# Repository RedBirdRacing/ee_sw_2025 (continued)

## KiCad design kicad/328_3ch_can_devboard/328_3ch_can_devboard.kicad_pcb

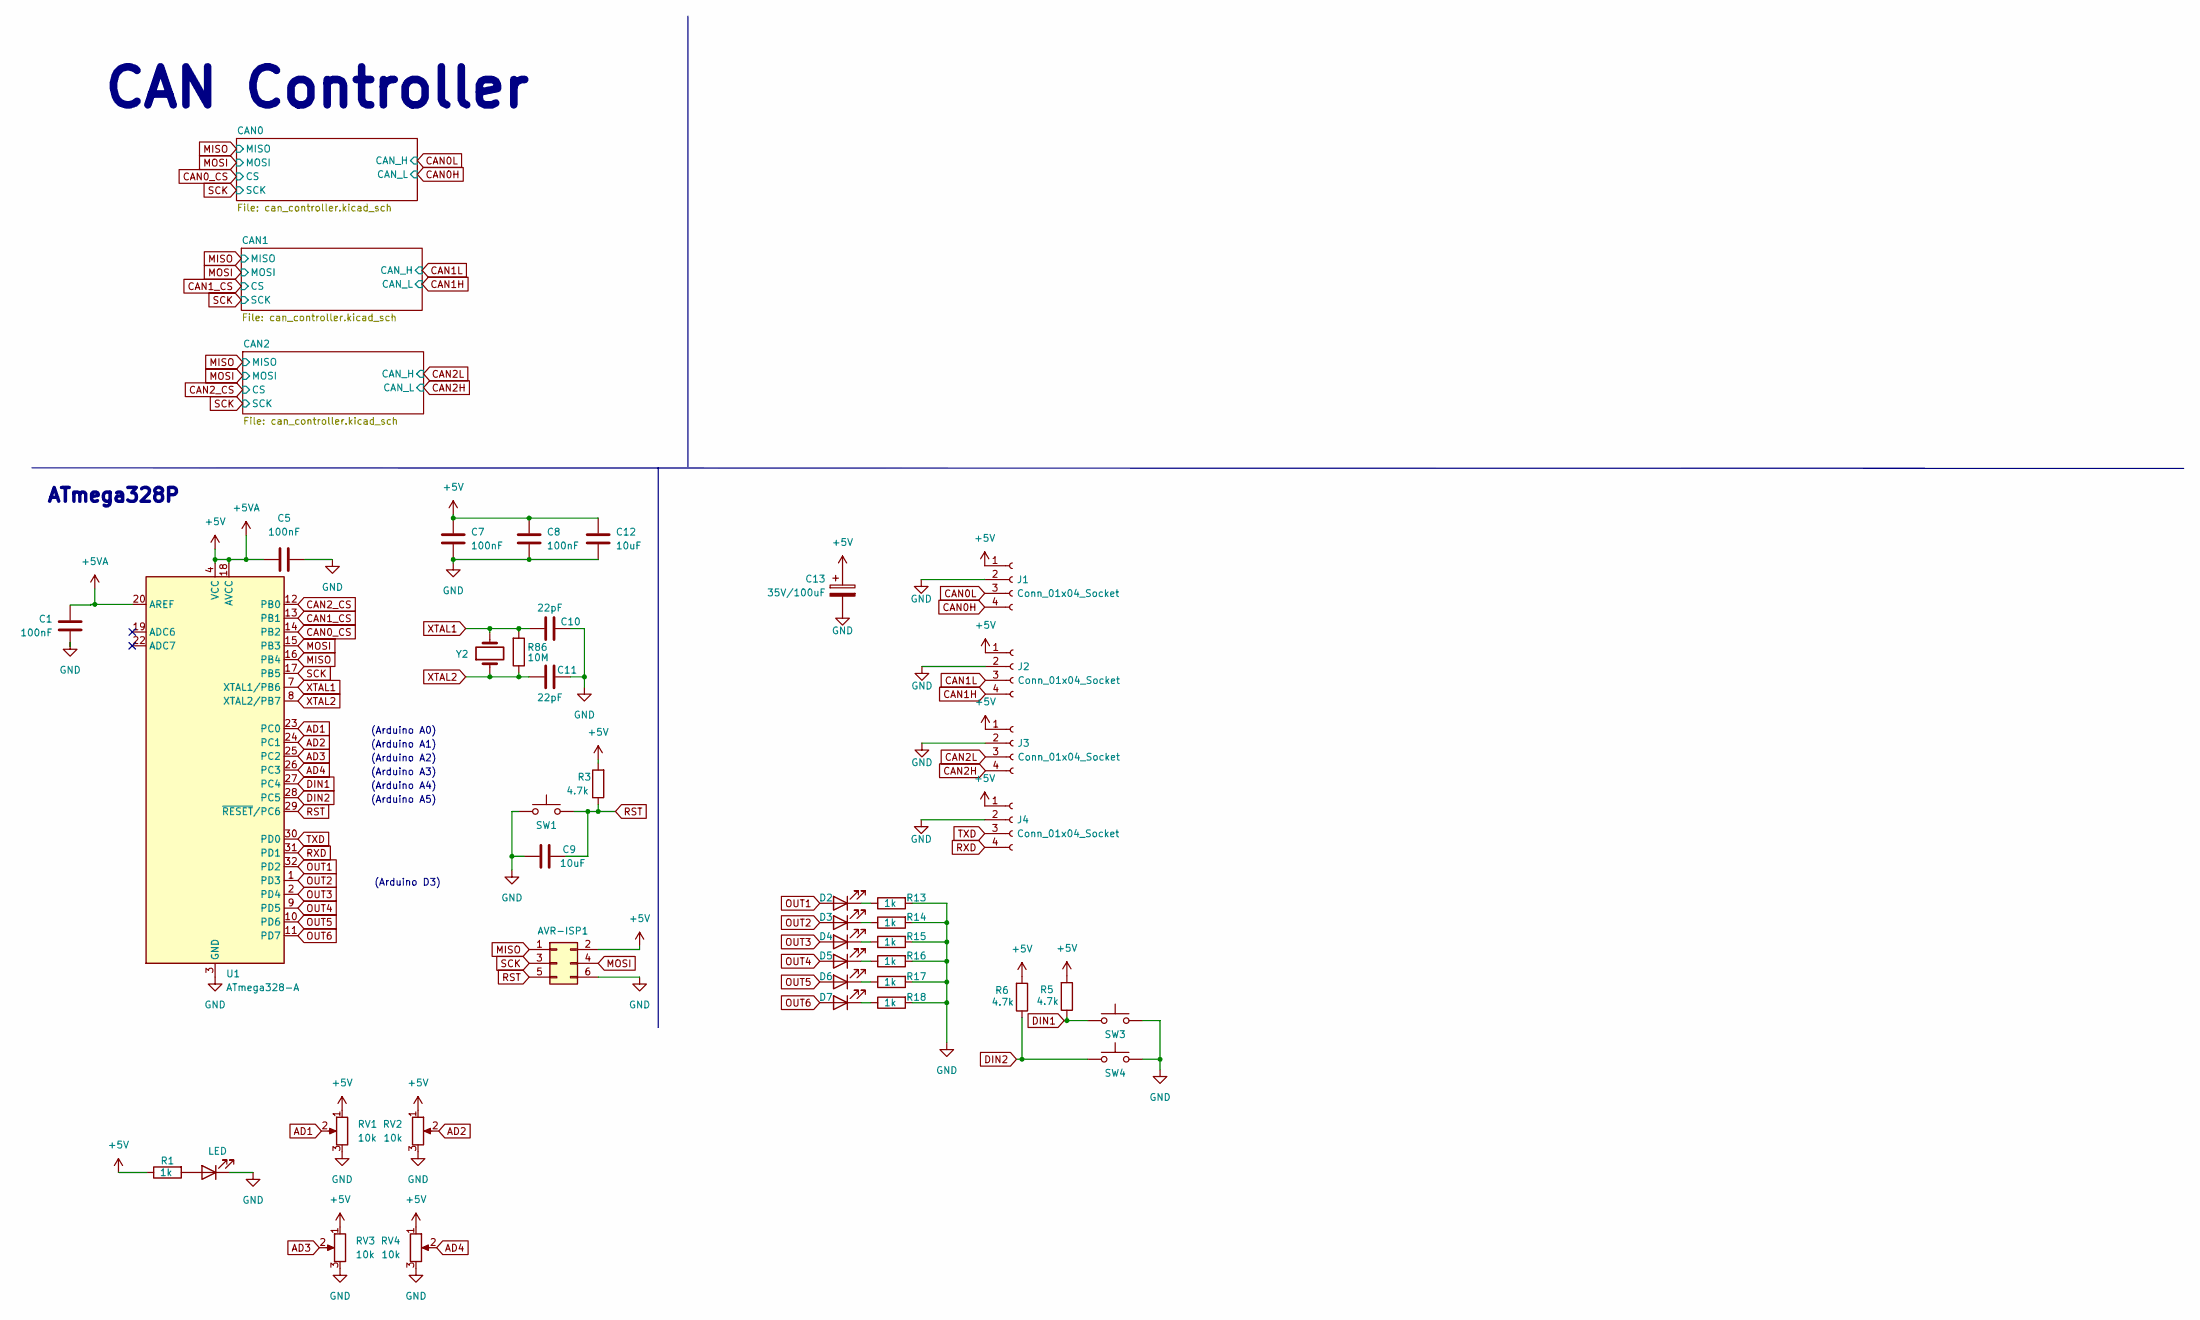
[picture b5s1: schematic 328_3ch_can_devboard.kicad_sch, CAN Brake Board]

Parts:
AVR-ISP1: Conn_02x03_Odd_Even; PinHeader_2x03_P2.54mm_Vertical
C1, C5, C7, C8: 100nF; C_0805_2012Metric_Pad1.18x1.45mm_HandSolder_L
C9, C12: 10uF; C_0805_2012Metric_Pad1.18x1.45mm_HandSolder_L
C10, C11: 22pF; C_0805_2012Metric_Pad1.18x1.45mm_HandSolder_L
C13: 35V/100uF; CP_Radial_D6.3mm_P2.50mm
D1, D2, D3, D4, D5, D6, D7: LED; LED_0805_2012Metric_Pad1.15x1.40mm_HandSolder
J1, J2, J3, J4: Conn_01x04_Socket; JST_XH_B4B-XH-A_1x04_P2.50mm_Vertical
R1, R13, R14, R15, R16, R17, R18: 1k; R_0805_2012Metric_Pad1.20x1.40mm_HandSolder_L
R3, R5, R6: 4.7k; R_0805_2012Metric_Pad1.20x1.40mm_HandSolder_L
R86: 10M; R_0805_2012Metric_Pad1.20x1.40mm_HandSolder_L
RV1, RV2, RV3, RV4: 10k; TRIM_3362P-1-103
SW1: SW_Push; SW_SPST_CK_RS282G05A3
SW3, SW4: SW_Push; SW_PUSH_6mm_H5mm
U1: ATmega328-A; TQFP-32_7x7mm_P0.8mm_L
Y2: 20MHz; Crystal_HC49-U_Vertical_W_SMD

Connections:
+5V: AVR-ISP1.2, C1.2, C5.2, C7.2, C8.2, C12.2, C13.1, J1.1, J2.1, J3.1, J4.1, R1.1, R3.2, R5.2, R6.2, RV1.1, RV2.1, RV3.1, RV4.1, U1.4 (VCC), U1.6 (VCC), U1.18 (AVCC), U1.20 (AREF); also elsewhere on the board
AD1: RV1.2, U1.23 (PC0)
AD2: RV2.2, U1.24 (PC1)
AD3: RV3.2, U1.25 (PC2)
AD4: RV4.2, U1.26 (PC3)
CAN0H: J1.4; also elsewhere on the board
CAN0L: J1.3; also elsewhere on the board
CAN0_CS: U1.14 (PB2); also elsewhere on the board
CAN1H: J2.4; also elsewhere on the board
CAN1L: J2.3; also elsewhere on the board
CAN1_CS: U1.13 (PB1); also elsewhere on the board
CAN2H: J3.4; also elsewhere on the board
CAN2L: J3.3; also elsewhere on the board
CAN2_CS: U1.12 (PB0); also elsewhere on the board
DIN1: R5.1, SW3.1, U1.27 (PC4)
DIN2: R6.1, SW4.1, U1.28 (PC5)
GND: AVR-ISP1.6, C1.1, C5.1, C7.1, C8.1, C9.1, C10.1, C11.1, C12.1, C13.2, D1.1 (K), J1.2, J2.2, J3.2, J4.2, R13.2, R14.2, R15.2, R16.2, R17.2, R18.2, RV1.3, RV2.3, RV3.3, RV4.3, SW1.1, SW3.2, SW4.2, U1.3 (GND), U1.5 (GND), U1.21 (GND); also elsewhere on the board
MISO: AVR-ISP1.1, U1.16 (PB4); also elsewhere on the board
MOSI: AVR-ISP1.4, U1.15 (PB3); also elsewhere on the board
unnamed: D1.2 (A), R1.2
unnamed: D2.1 (K), R13.1
unnamed: D3.1 (K), R14.1
unnamed: D4.1 (K), R15.1
unnamed: D5.1 (K), R16.1
unnamed: D6.1 (K), R17.1
unnamed: D7.1 (K), R18.1
OUT1: D2.2 (A), U1.32 (PD2)
OUT2: D3.2 (A), U1.1 (PD3)
OUT3: D4.2 (A), U1.2 (PD4)
OUT4: D5.2 (A), U1.9 (PD5)
OUT5: D6.2 (A), U1.10 (PD6)
OUT6: D7.2 (A), U1.11 (PD7)
RST: AVR-ISP1.5, C9.2, R3.1, SW1.2, U1.29 (~RESET/PC6)
RXD: J4.4, U1.31 (PD1)
SCK: AVR-ISP1.3, U1.17 (PB5); also elsewhere on the board
TXD: J4.3, U1.30 (PD0)
XTAL1: C10.2, R86.2, U1.7 (XTAL1/PB6), Y2.2
XTAL2: C11.2, R86.1, U1.8 (XTAL2/PB7), Y2.1

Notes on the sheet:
(Arduino A4)
(Arduino A2)
ATmega328P
(Arduino A0)
(Arduino D3)
(Arduino A5)
CAN Controller
(Arduino A1)
(Arduino A3)

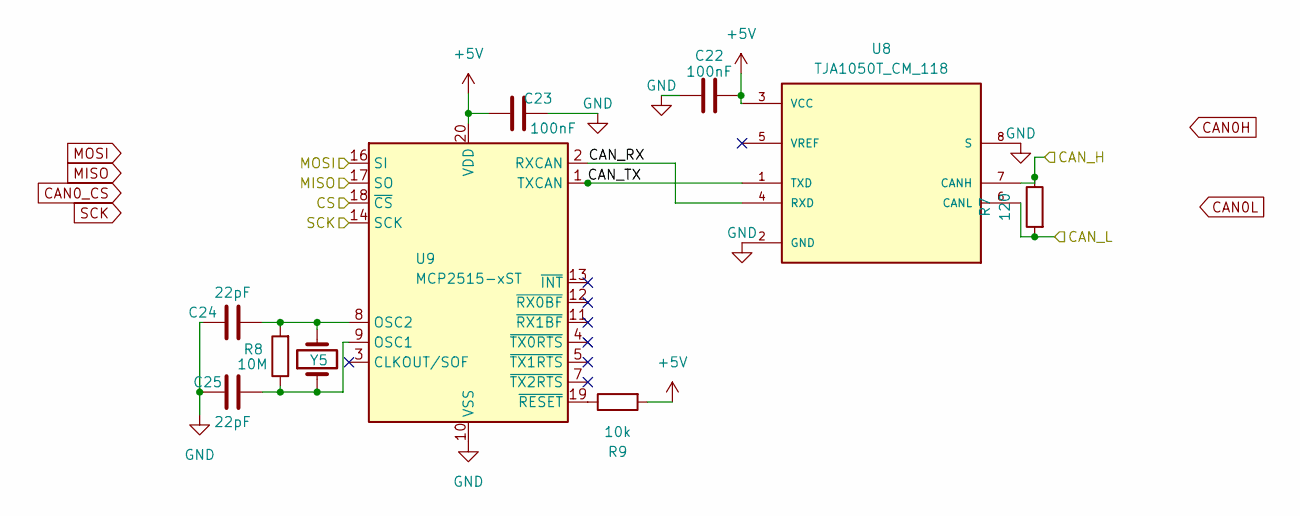
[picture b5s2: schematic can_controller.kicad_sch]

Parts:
C22, C23: 100nF; C_0805_2012Metric_Pad1.18x1.45mm_HandSolder_L
C24, C25: 22pF; C_0805_2012Metric_Pad1.18x1.45mm_HandSolder_L
R7: 120; R_0805_2012Metric_Pad1.20x1.40mm_HandSolder_L
R8: 10M; R_0805_2012Metric_Pad1.20x1.40mm_HandSolder_L
R9: 10k; R_0805_2012Metric_Pad1.20x1.40mm_HandSolder_L
U8: TJA1050T_CM_118; SOIC127P600X175-8N; PARTREV 4
U9: MCP2515-xST; TSSOP-20_4.4x6.5mm_P0.65mm
Y5: 20MHz; Crystal_HC49-U_Vertical_W_SMD

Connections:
+5V: C22.2, C23.2, R9.2, U8.3 (VCC), U9.20 (VDD); also elsewhere on the board
/CAN0/CAN_RX: U8.4 (RXD), U9.2 (RXCAN)
/CAN0/CAN_TX: U8.1 (TXD), U9.1 (TXCAN)
CAN0H: R7.2, U8.6 (CANL); also elsewhere on the board
CAN0L: R7.1, U8.7 (CANH); also elsewhere on the board
CAN0_CS: U9.18 (~CS); also elsewhere on the board
GND: C22.1, C23.1, C24.1, C25.1, U8.2 (GND), U8.8 (S), U9.10 (VSS); also elsewhere on the board
MISO: U9.17 (SO); also elsewhere on the board
MOSI: U9.16 (SI); also elsewhere on the board
unnamed: C25.2, R8.1, U9.9 (OSC1), Y5.1
unnamed: C24.2, R8.2, U9.8 (OSC2), Y5.2
unnamed: R9.1, U9.19 (~RESET)
SCK: U9.14 (SCK); also elsewhere on the board

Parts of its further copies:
C2, C3, C14, C15: 100nF; C_0805_2012Metric_Pad1.18x1.45mm_HandSolder_L
C4, C6, C16, C17: 22pF; C_0805_2012Metric_Pad1.18x1.45mm_HandSolder_L
R2, R11: 120; R_0805_2012Metric_Pad1.20x1.40mm_HandSolder_L
R4, R12: 10M; R_0805_2012Metric_Pad1.20x1.40mm_HandSolder_L
R10, R19: 10k; R_0805_2012Metric_Pad1.20x1.40mm_HandSolder_L
U2, U4: TJA1050T_CM_118; SOIC127P600X175-8N; PARTREV 4
U3, U5: MCP2515-xST; TSSOP-20_4.4x6.5mm_P0.65mm
Y1, Y3: 20MHz; Crystal_HC49-U_Vertical_W_SMD

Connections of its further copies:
+5V: C2.2, C3.2, C14.2, C15.2, R10.2, R19.2, U2.3 (VCC), U3.20 (VDD), U4.3 (VCC), U5.20 (VDD); also elsewhere on the board
/CAN1/CAN_RX: U2.4 (RXD), U3.2 (RXCAN)
/CAN1/CAN_TX: U2.1 (TXD), U3.1 (TXCAN)
/CAN2/CAN_RX: U4.4 (RXD), U5.2 (RXCAN)
/CAN2/CAN_TX: U4.1 (TXD), U5.1 (TXCAN)
CAN1H: R2.2, U2.6 (CANL); also elsewhere on the board
CAN1L: R2.1, U2.7 (CANH); also elsewhere on the board
CAN1_CS: U3.18 (~CS); also elsewhere on the board
CAN2H: R11.2, U4.6 (CANL); also elsewhere on the board
CAN2L: R11.1, U4.7 (CANH); also elsewhere on the board
CAN2_CS: U5.18 (~CS); also elsewhere on the board
GND: C2.1, C3.1, C4.1, C6.1, C14.1, C15.1, C16.1, C17.1, U2.2 (GND), U2.8 (S), U3.10 (VSS), U4.2 (GND), U4.8 (S), U5.10 (VSS); also elsewhere on the board
MISO: U3.17 (SO), U5.17 (SO); also elsewhere on the board
MOSI: U3.16 (SI), U5.16 (SI); also elsewhere on the board
unnamed: C6.2, R4.1, U3.9 (OSC1), Y1.1
unnamed: C4.2, R4.2, U3.8 (OSC2), Y1.2
unnamed: R10.1, U3.19 (~RESET)
unnamed: C17.2, R12.1, U5.9 (OSC1), Y3.1
unnamed: C16.2, R12.2, U5.8 (OSC2), Y3.2
unnamed: R19.1, U5.19 (~RESET)
SCK: U3.14 (SCK), U5.14 (SCK); also elsewhere on the board

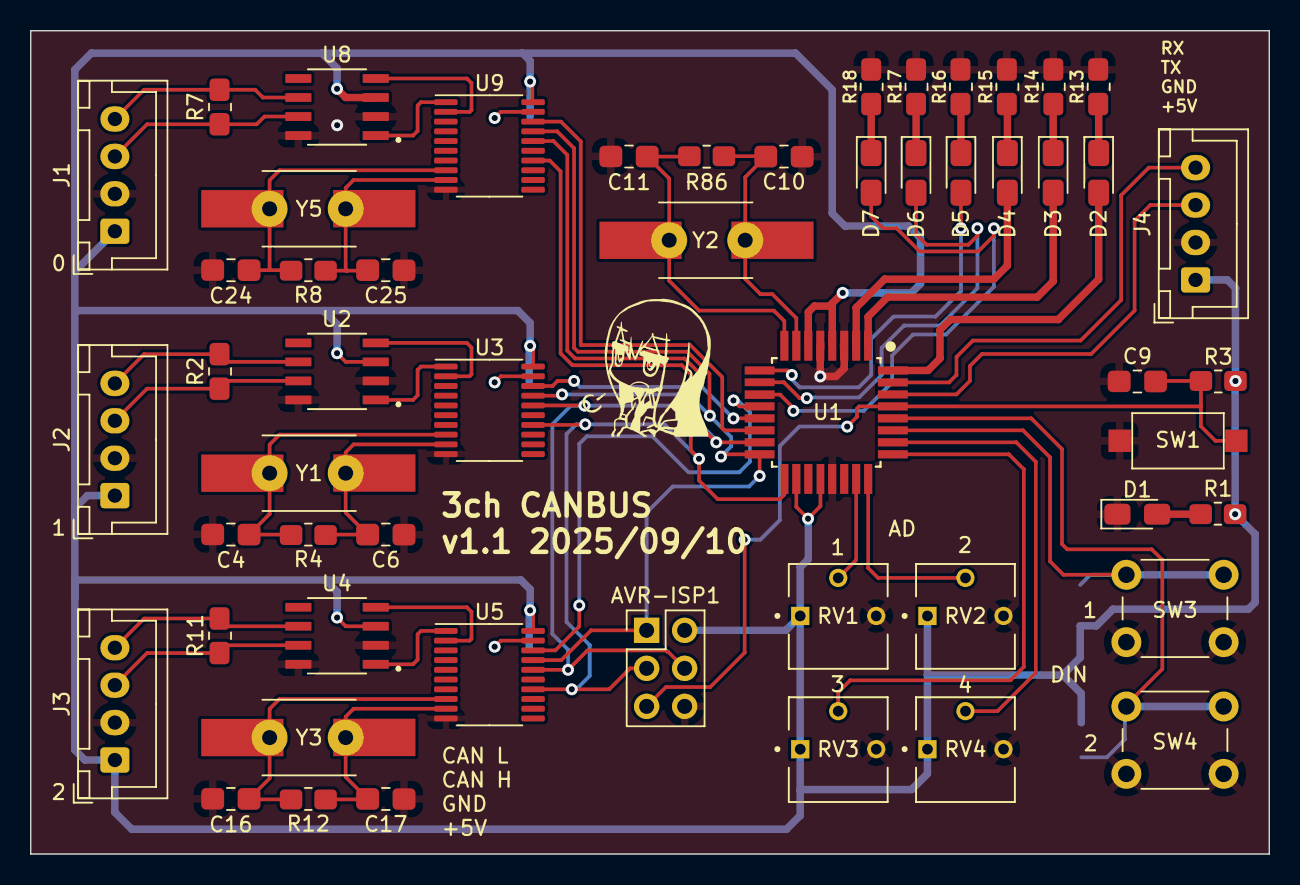
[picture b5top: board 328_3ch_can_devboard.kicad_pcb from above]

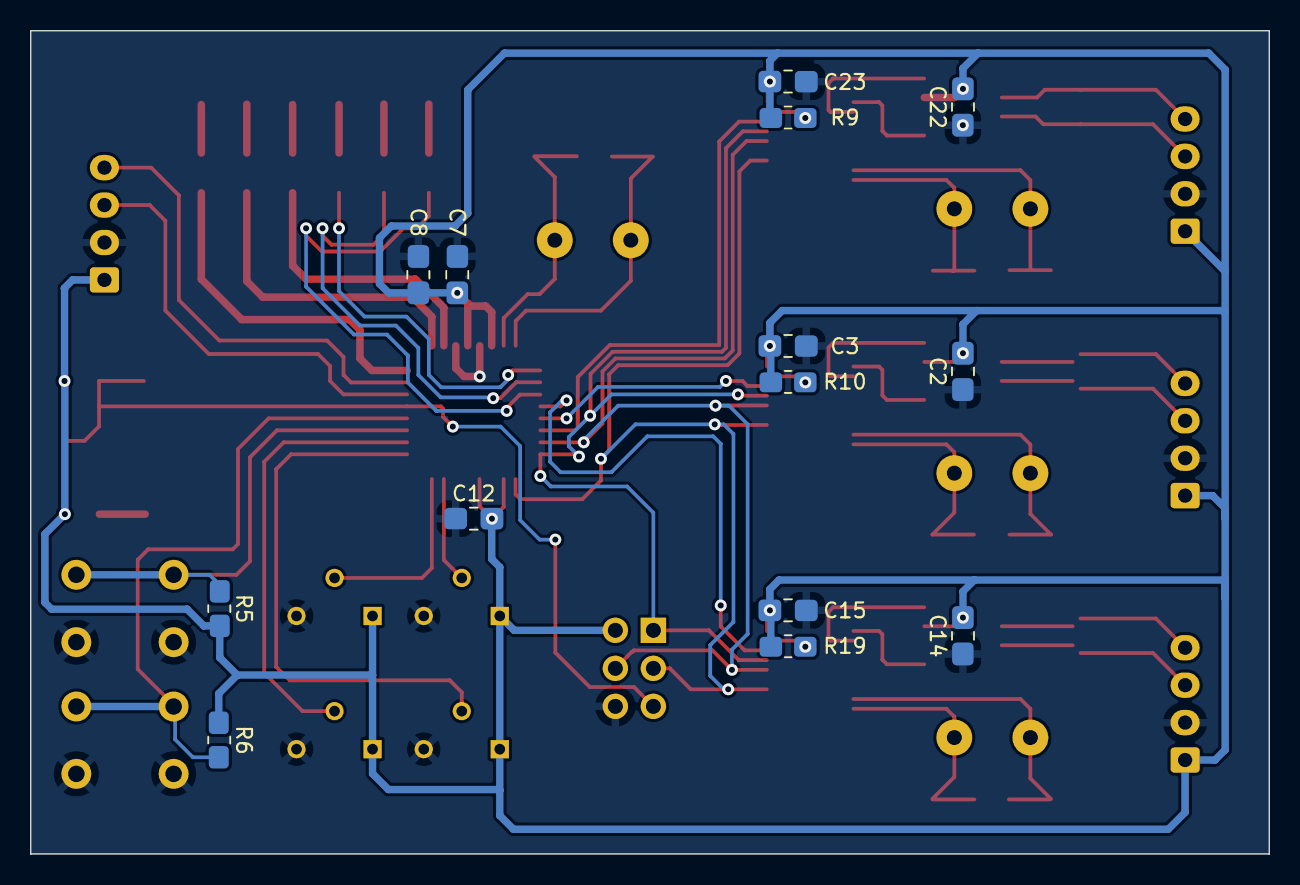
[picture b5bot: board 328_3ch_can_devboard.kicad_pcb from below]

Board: 2 copper layers, 82.8 x 55.0 mm, 69 parts (14 on the bottom side), 53 nets.

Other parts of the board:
G0: LOGO

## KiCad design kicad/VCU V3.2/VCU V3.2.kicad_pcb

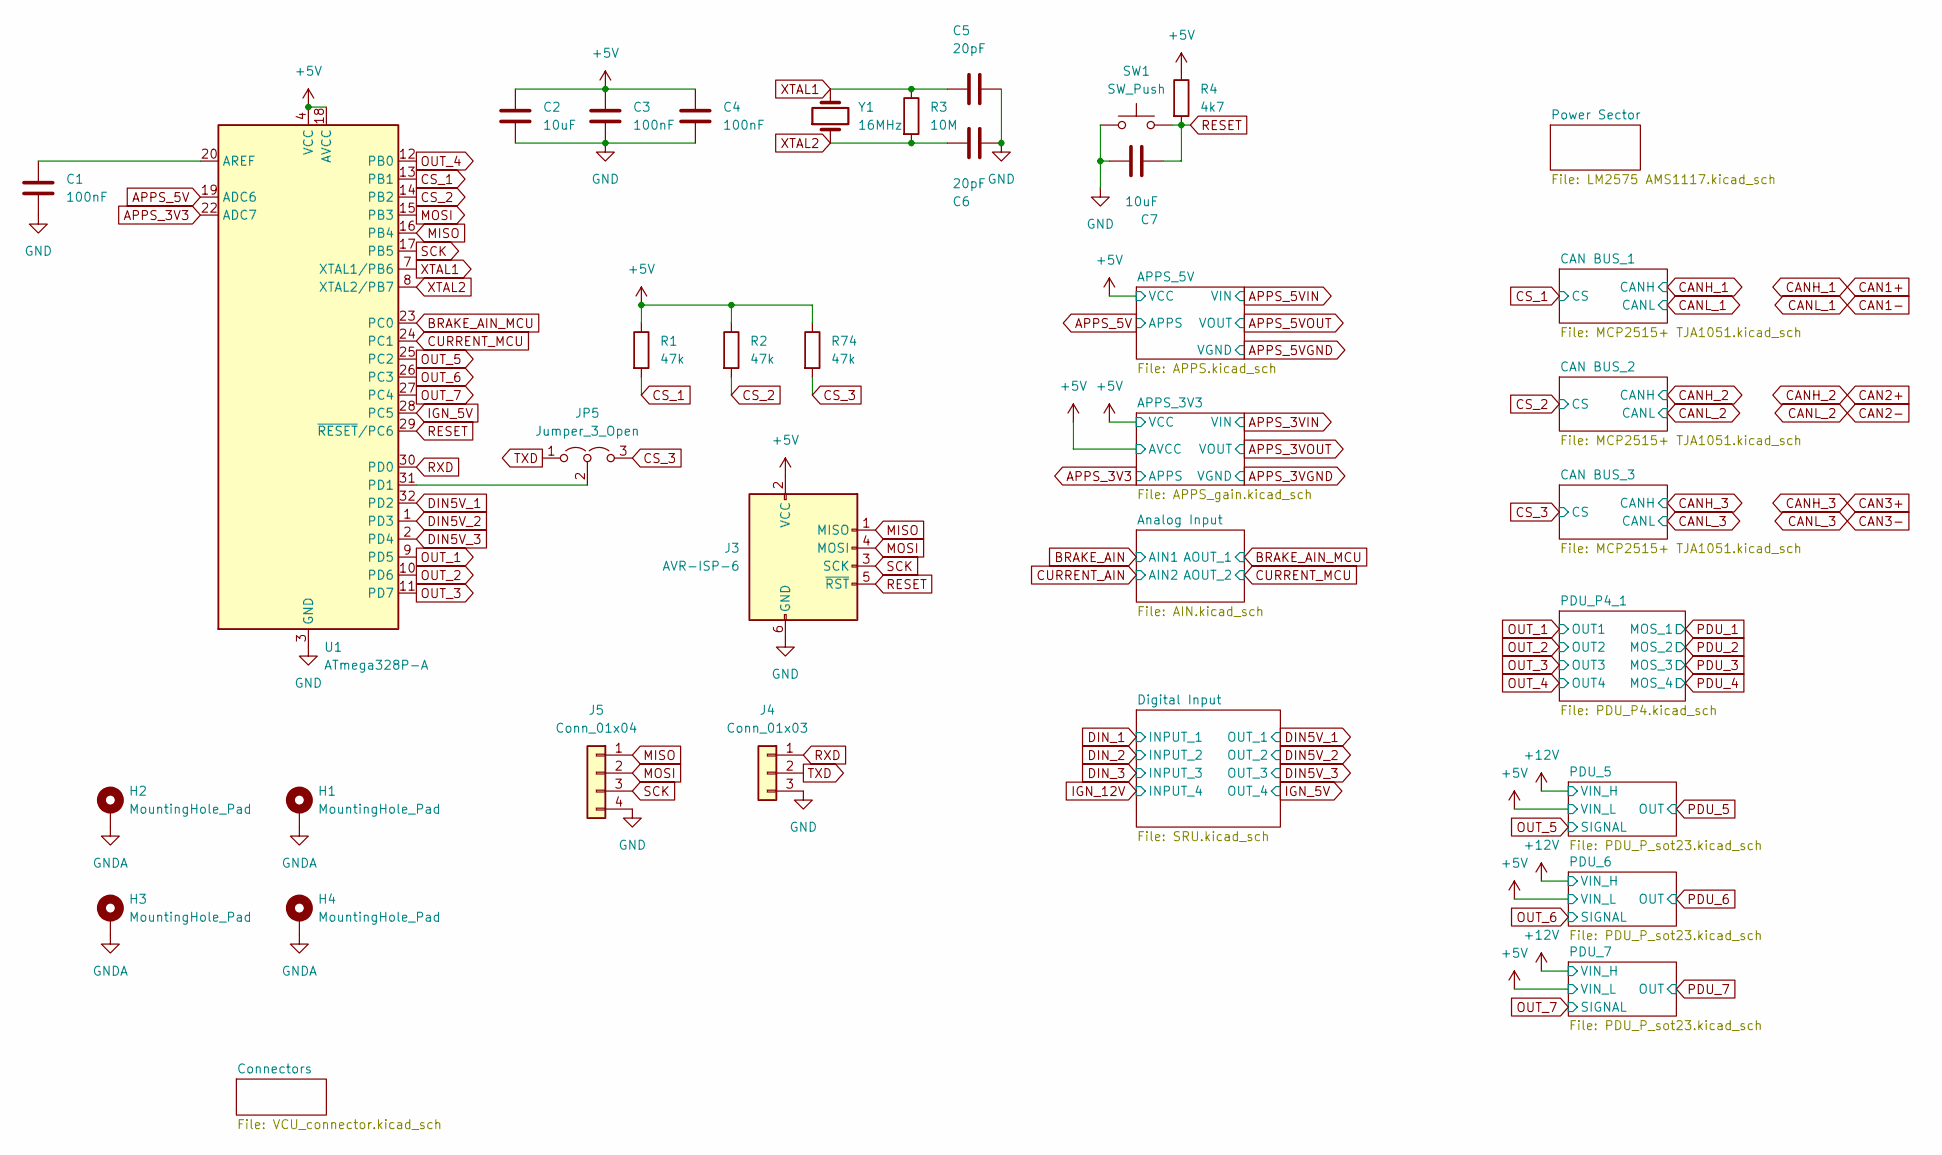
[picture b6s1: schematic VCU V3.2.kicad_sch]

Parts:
C1, C3, C4: 100nF; C_0805_2012Metric_Pad1.18x1.45mm_HandSolder_L
C2, C7: 10uF; C_0805_2012Metric_Pad1.18x1.45mm_HandSolder_L
C5, C6: 20pF; C_0805_2012Metric_Pad1.18x1.45mm_HandSolder_L
H1, H2, H3, H4: MountingHole_Pad; MountingHole_3.2mmx5mm_M3_ISO7380
J3: AVR-ISP-6; PinHeader_2x03_P2.54mm_Vertical_handsolder
J4: Conn_01x03; JST_XH_B3B-XH-A_1x03_P2.50mm_Vertical
J5: Conn_01x04; JST_XH_B4B-XH-A_1x04_P2.50mm_Vertical
JP5: Jumper_3_Open; SolderJumper-3_P1.3mm_Open_Pad1.0x1.5mm
R1, R2, R74: 47k; R_0805_2012Metric_Pad1.20x1.40mm_HandSolder_L
R3: 10M; R_0805_2012Metric_Pad1.20x1.40mm_HandSolder_L
R4: 4k7; R_0805_2012Metric_Pad1.20x1.40mm_HandSolder_L
SW1: SW_Push; SW_PUSH_6mm
U1: ATmega328P-A; TQFP-32_7x7mm_P0.8mm_L
Y1: 16MHz; Crystal_HC49-U_Vertical_W_SMD_Handolder

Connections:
+5V: C2.1, C3.1, C4.1, J3.2 (VCC), R1.1, R2.1, R4.1, R74.1, U1.4 (VCC), U1.6 (VCC), U1.18 (AVCC); also elsewhere on the board
APPS_3V3: U1.22 (ADC7); also elsewhere on the board
APPS_5V: U1.19 (ADC6); also elsewhere on the board
BRAKE_AIN_MCU: U1.23 (PC0); also elsewhere on the board
CS_1: R1.2, U1.13 (PB1); also elsewhere on the board
CS_2: R2.2, U1.14 (PB2); also elsewhere on the board
CS_3: JP5.3 (B), R74.2; also elsewhere on the board
CURRENT_MCU: U1.24 (PC1); also elsewhere on the board
DIN5V_1: U1.32 (PD2); also elsewhere on the board
DIN5V_2: U1.1 (PD3); also elsewhere on the board
DIN5V_3: U1.2 (PD4); also elsewhere on the board
GND: C1.2, C2.2, C3.2, C4.2, C5.2, C6.2, C7.2, J3.6 (GND), J4.3, J5.4, SW1.1, U1.3 (GND), U1.5 (GND), U1.21 (GND); also elsewhere on the board
IGN_5V: U1.28 (PC5); also elsewhere on the board
MISO: J3.1 (MISO), J5.1, U1.16 (PB4); also elsewhere on the board
MOSI: J3.4 (MOSI), J5.2, U1.15 (PB3); also elsewhere on the board
unnamed: JP5.2 (C), U1.31 (PD1)
unnamed: C1.1, U1.20 (AREF)
OUT_1: U1.9 (PD5); also elsewhere on the board
OUT_2: U1.10 (PD6); also elsewhere on the board
OUT_3: U1.11 (PD7); also elsewhere on the board
OUT_4: U1.12 (PB0); also elsewhere on the board
OUT_5: U1.25 (PC2); also elsewhere on the board
OUT_6: U1.26 (PC3); also elsewhere on the board
OUT_7: U1.27 (PC4); also elsewhere on the board
RESET: C7.1, J3.5 (~RST), R4.2, SW1.2, U1.29 (~RESET/PC6)
RXD: J4.1, U1.30 (PD0)
SCK: J3.3 (SCK), J5.3, U1.17 (PB5); also elsewhere on the board
TXD: J4.2, JP5.1 (A)
XTAL1: C5.1, R3.1, U1.7 (XTAL1/PB6), Y1.2
XTAL2: C6.1, R3.2, U1.8 (XTAL2/PB7), Y1.1

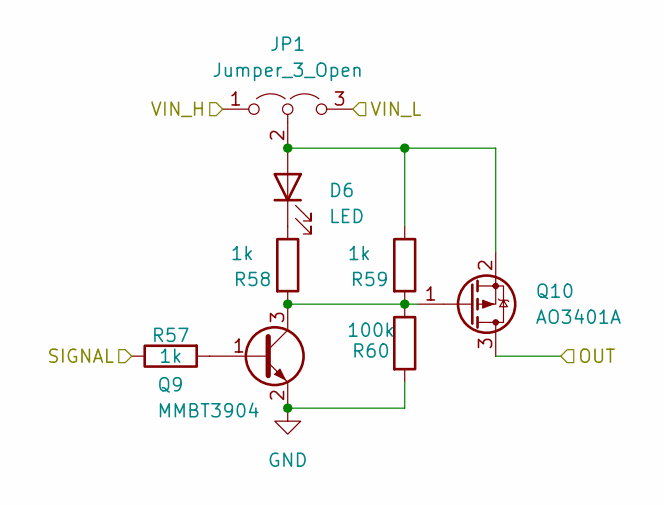
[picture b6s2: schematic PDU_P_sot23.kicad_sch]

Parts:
D6: LED; LED_0805_2012Metric_Pad1.45x1.40mm_HandSolder
JP1: Jumper_3_Open; SolderJumper-3_P1.3mm_Open_Pad1.0x1.5mm
Q9: MMBT3904; SOT-23
Q10: AO3401A; SOT-23
R57, R58, R59: 1k; R_0805_2012Metric_Pad1.20x1.40mm_HandSolder_L
R60: 100k; R_0805_2012Metric_Pad1.20x1.40mm_HandSolder_L

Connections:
+5V: JP1.3 (B); also elsewhere on the board
+12V: JP1.1 (A); also elsewhere on the board
GND: Q9.2 (E), R60.2; also elsewhere on the board
unnamed: D6.2 (A), JP1.2 (C), Q10.2 (S), R59.1
unnamed: D6.1 (K), R58.1
unnamed: Q9.1 (B), R57.2
unnamed: Q9.3 (C), Q10.1 (G), R58.2, R59.2, R60.1
OUT_5: R57.1; also elsewhere on the board
PDU_5: Q10.3 (D); also elsewhere on the board

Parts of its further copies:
D7, D8: LED; LED_0805_2012Metric_Pad1.45x1.40mm_HandSolder
JP2, JP3: Jumper_3_Open; SolderJumper-3_P1.3mm_Open_Pad1.0x1.5mm
Q11, Q13: MMBT3904; SOT-23
Q12, Q14: AO3401A; SOT-23
R61, R62, R63, R65, R66, R67: 1k; R_0805_2012Metric_Pad1.20x1.40mm_HandSolder_L
R64, R68: 100k; R_0805_2012Metric_Pad1.20x1.40mm_HandSolder_L

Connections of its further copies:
+5V: JP2.3 (B), JP3.3 (B); also elsewhere on the board
+12V: JP2.1 (A), JP3.1 (A); also elsewhere on the board
GND: Q11.2 (E), Q13.2 (E), R64.2, R68.2; also elsewhere on the board
unnamed: D7.2 (A), JP2.2 (C), Q12.2 (S), R63.1
unnamed: D7.1 (K), R62.1
unnamed: D8.2 (A), JP3.2 (C), Q14.2 (S), R67.1
unnamed: D8.1 (K), R66.1
unnamed: Q11.1 (B), R61.2
unnamed: Q11.3 (C), Q12.1 (G), R62.2, R63.2, R64.1
unnamed: Q13.1 (B), R65.2
unnamed: Q13.3 (C), Q14.1 (G), R66.2, R67.2, R68.1
OUT_6: R61.1; also elsewhere on the board
OUT_7: R65.1; also elsewhere on the board
PDU_6: Q12.3 (D); also elsewhere on the board
PDU_7: Q14.3 (D); also elsewhere on the board

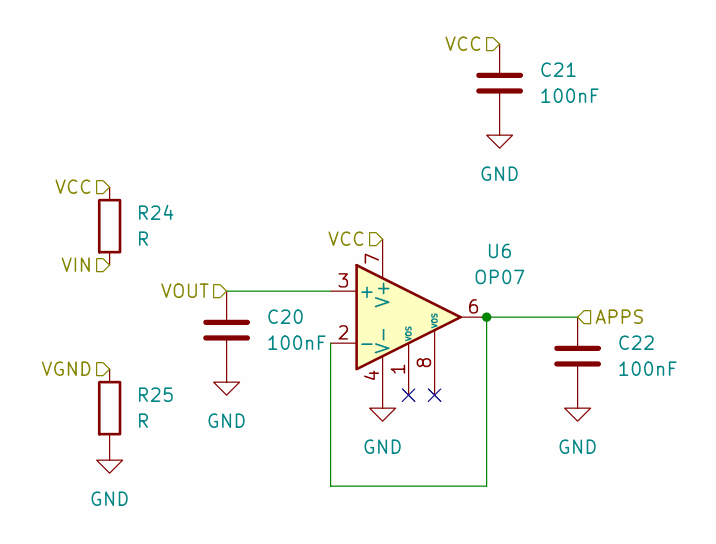
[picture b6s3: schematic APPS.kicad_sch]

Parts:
C20, C21, C22: 100nF; C_0805_2012Metric_Pad1.18x1.45mm_HandSolder_L
R24, R25: R; R_0805_2012Metric_Pad1.20x1.40mm_HandSolder_L
U6: OP07; SOIC-8_3.9x4.9mm_P1.27mm_RMC_Handsolder

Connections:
+5V: C21.1, R24.1, U6.7 (V+); also elsewhere on the board
APPS_5V: C22.1, U6.2 (-), U6.6; also elsewhere on the board
APPS_5VGND: R25.1; also elsewhere on the board
APPS_5VIN: R24.2; also elsewhere on the board
APPS_5VOUT: C20.1, U6.3 (+); also elsewhere on the board
GND: C20.2, C21.2, C22.2, R25.2, U6.4 (V-); also elsewhere on the board

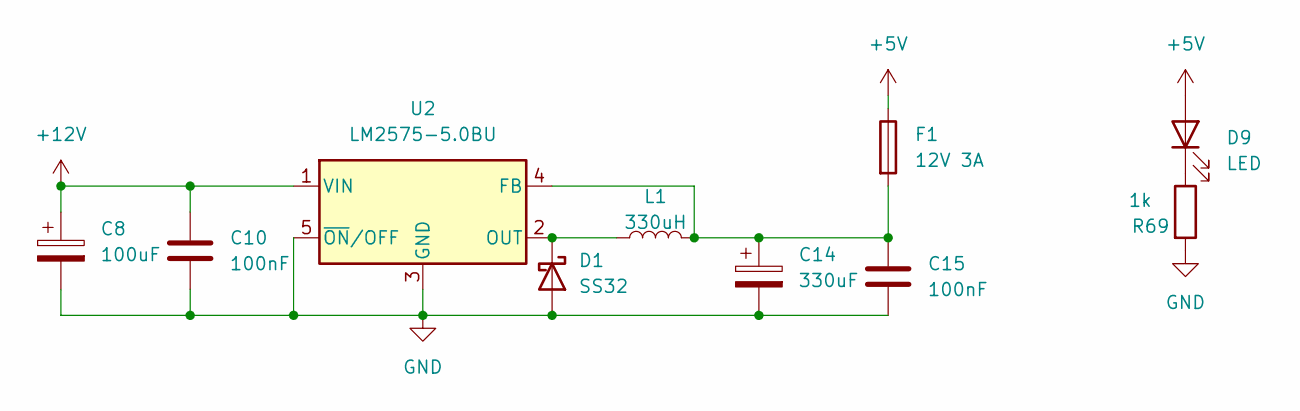
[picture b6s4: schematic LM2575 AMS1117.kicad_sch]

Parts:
C8: 100uF; CP_Radial_D6.3mm_P2.50mm_handsolder
C10, C15: 100nF; C_0805_2012Metric_Pad1.18x1.45mm_HandSolder_L
C14: 330uF; CP_Radial_D6.3mm_P2.50mm_handsolder
D1: SS32; D_SMA_Handsoldering
D9: LED; LED_0805_2012Metric_Pad1.45x1.40mm_HandSolder
F1: 12V 3A; Fuse_1210_3225Metric_Pad1.42x2.65mm_HandSolder
L1: 330uH; L_TDK_SLF12575
R69: 1k; R_0805_2012Metric_Pad1.20x1.40mm_HandSolder_L
U2: LM2575-5.0BU; TO-263-5_TabPin3_Long

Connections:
+5V: D9.2 (A), F1.1; also elsewhere on the board
+12V: C8.1, C10.1, U2.1 (VIN); also elsewhere on the board
GND: C8.2, C10.2, C14.2, C15.2, D1.2 (A), R69.2, U2.3 (GND), U2.5 (~ON/OFF); also elsewhere on the board
unnamed: D1.1 (K), L1.1, U2.2 (OUT)
unnamed: D9.1 (K), R69.1
unnamed: C14.1, C15.1, F1.2, L1.2, U2.4 (FB)

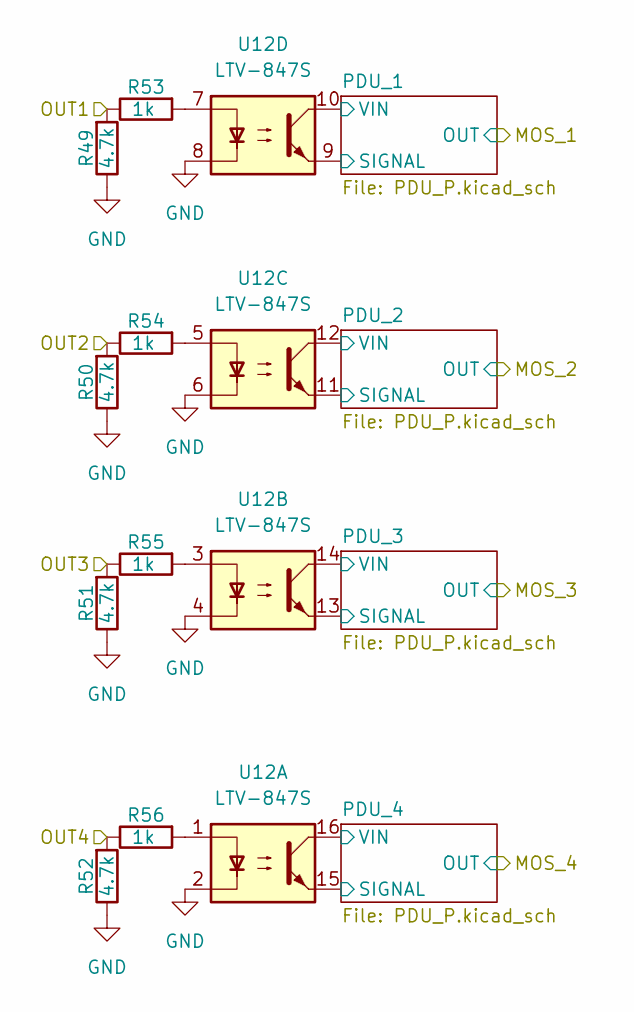
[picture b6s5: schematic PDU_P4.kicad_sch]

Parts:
R49, R50, R51, R52: 4.7k; R_0805_2012Metric_Pad1.20x1.40mm_HandSolder_L
R53, R54, R55, R56: 1k; R_0805_2012Metric_Pad1.20x1.40mm_HandSolder_L
U12: LTV-847S; SMDIP-16_W9.53mm

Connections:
+12V: U12.10, U12.12, U12.14, U12.16; also elsewhere on the board
/PDU_P4_1/PDU_1/SIGNAL: U12.9; also elsewhere on the board
/PDU_P4_1/PDU_2/SIGNAL: U12.11; also elsewhere on the board
/PDU_P4_1/PDU_3/SIGNAL: U12.13; also elsewhere on the board
/PDU_P4_1/PDU_4/SIGNAL: U12.15; also elsewhere on the board
GND: R49.1, R50.1, R51.1, R52.1, U12.2, U12.4, U12.6, U12.8; also elsewhere on the board
unnamed: R53.2, U12.7
unnamed: R54.2, U12.5
unnamed: R55.2, U12.3
unnamed: R56.2, U12.1
OUT_1: R49.2, R53.1; also elsewhere on the board
OUT_2: R50.2, R54.1; also elsewhere on the board
OUT_3: R51.2, R55.1; also elsewhere on the board
OUT_4: R52.2, R56.1; also elsewhere on the board

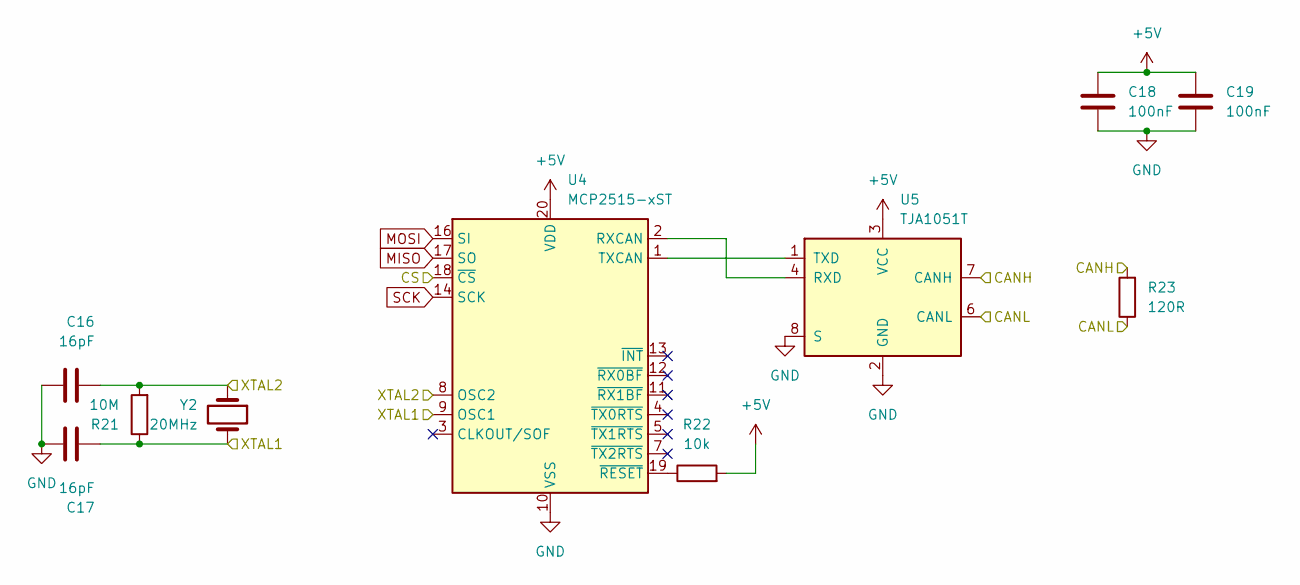
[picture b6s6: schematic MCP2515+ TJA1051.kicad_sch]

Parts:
C16, C17: 16pF; C_0805_2012Metric_Pad1.18x1.45mm_HandSolder_L
C18, C19: 100nF; C_0805_2012Metric_Pad1.18x1.45mm_HandSolder_L
R21: 10M; R_0805_2012Metric_Pad1.20x1.40mm_HandSolder_L
R22: 10k; R_0805_2012Metric_Pad1.20x1.40mm_HandSolder_L
R23: 120R; R_0805_2012Metric_Pad1.20x1.40mm_HandSolder_L
U4: MCP2515-xST; TSSOP-20_4.4x6.5mm_P0.65mm
U5: TJA1051T; SOIC-8_3.9x4.9mm_P1.27mm_RMC_Handsolder
Y2: 20MHz; Crystal_HC49-U_Vertical_W_SMD_Handolder

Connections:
+5V: C18.2, C19.2, R22.2, U4.20 (VDD), U5.3 (VCC); also elsewhere on the board
/CAN BUS_1/XTAL1: C17.1, R21.1, U4.9 (OSC1), Y2.2
/CAN BUS_1/XTAL2: C16.1, R21.2, U4.8 (OSC2), Y2.1
CAN1+: R23.2, U5.7 (CANH); also elsewhere on the board
CAN1-: R23.1, U5.6 (CANL); also elsewhere on the board
CS_1: U4.18 (~CS); also elsewhere on the board
GND: C16.2, C17.2, C18.1, C19.1, U4.10 (VSS), U5.2 (GND), U5.8 (S); also elsewhere on the board
MISO: U4.17 (SO); also elsewhere on the board
MOSI: U4.16 (SI); also elsewhere on the board
unnamed: U4.2 (RXCAN), U5.4 (RXD)
unnamed: U4.1 (TXCAN), U5.1 (TXD)
unnamed: R22.1, U4.19 (~RESET)
SCK: U4.14 (SCK); also elsewhere on the board

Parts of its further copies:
C26, C27, C33, C34: 16pF; C_0805_2012Metric_Pad1.18x1.45mm_HandSolder_L
C28, C29, C35, C36: 100nF; C_0805_2012Metric_Pad1.18x1.45mm_HandSolder_L
R30, R71: 10M; R_0805_2012Metric_Pad1.20x1.40mm_HandSolder_L
R31, R72: 10k; R_0805_2012Metric_Pad1.20x1.40mm_HandSolder_L
R32, R73: 120R; R_0805_2012Metric_Pad1.20x1.40mm_HandSolder_L
U8, U14: MCP2515-xST; TSSOP-20_4.4x6.5mm_P0.65mm
U9, U15: TJA1051T; SOIC-8_3.9x4.9mm_P1.27mm_RMC_Handsolder
Y3, Y4: 20MHz; Crystal_HC49-U_Vertical_W_SMD_Handolder

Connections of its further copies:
+5V: C28.2, C29.2, C35.2, C36.2, R31.2, R72.2, U8.20 (VDD), U9.3 (VCC), U14.20 (VDD), U15.3 (VCC); also elsewhere on the board
/CAN BUS_2/XTAL1: C27.1, R30.1, U8.9 (OSC1), Y3.2
/CAN BUS_2/XTAL2: C26.1, R30.2, U8.8 (OSC2), Y3.1
/CAN BUS_3/XTAL1: C34.1, R71.1, U14.9 (OSC1), Y4.2
/CAN BUS_3/XTAL2: C33.1, R71.2, U14.8 (OSC2), Y4.1
CAN2+: R32.2, U9.7 (CANH); also elsewhere on the board
CAN2-: R32.1, U9.6 (CANL); also elsewhere on the board
CAN3+: R73.2, U15.7 (CANH); also elsewhere on the board
CAN3-: R73.1, U15.6 (CANL); also elsewhere on the board
CS_2: U8.18 (~CS); also elsewhere on the board
CS_3: U14.18 (~CS); also elsewhere on the board
GND: C26.2, C27.2, C28.1, C29.1, C33.2, C34.2, C35.1, C36.1, U8.10 (VSS), U9.2 (GND), U9.8 (S), U14.10 (VSS), U15.2 (GND), U15.8 (S); also elsewhere on the board
MISO: U8.17 (SO), U14.17 (SO); also elsewhere on the board
MOSI: U8.16 (SI), U14.16 (SI); also elsewhere on the board
unnamed: U8.2 (RXCAN), U9.4 (RXD)
unnamed: U8.1 (TXCAN), U9.1 (TXD)
unnamed: R31.1, U8.19 (~RESET)
unnamed: U14.2 (RXCAN), U15.4 (RXD)
unnamed: U14.1 (TXCAN), U15.1 (TXD)
unnamed: R72.1, U14.19 (~RESET)
SCK: U8.14 (SCK), U14.14 (SCK); also elsewhere on the board

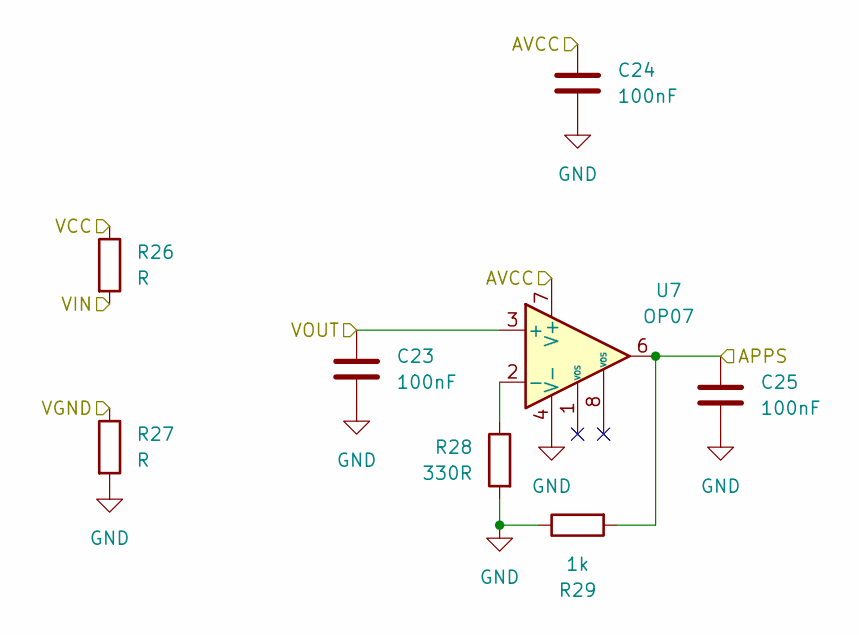
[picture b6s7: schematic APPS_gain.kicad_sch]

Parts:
C23, C24, C25: 100nF; C_0805_2012Metric_Pad1.18x1.45mm_HandSolder_L
R26, R27: R; R_0805_2012Metric_Pad1.20x1.40mm_HandSolder_L
R28: 330R; R_0805_2012Metric_Pad1.20x1.40mm_HandSolder_L
R29: 1k; R_0805_2012Metric_Pad1.20x1.40mm_HandSolder_L
U7: OP07; SOIC-8_3.9x4.9mm_P1.27mm_RMC_Handsolder

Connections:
+5V: C24.1, R26.1, U7.7 (V+); also elsewhere on the board
APPS_3V3: C25.1, R29.2, U7.6; also elsewhere on the board
APPS_3VGND: R27.1; also elsewhere on the board
APPS_3VIN: R26.2; also elsewhere on the board
APPS_3VOUT: C23.1, U7.3 (+); also elsewhere on the board
GND: C23.2, C24.2, C25.2, R27.2, R28.2, R29.1, U7.4 (V-); also elsewhere on the board
unnamed: R28.1, U7.2 (-)

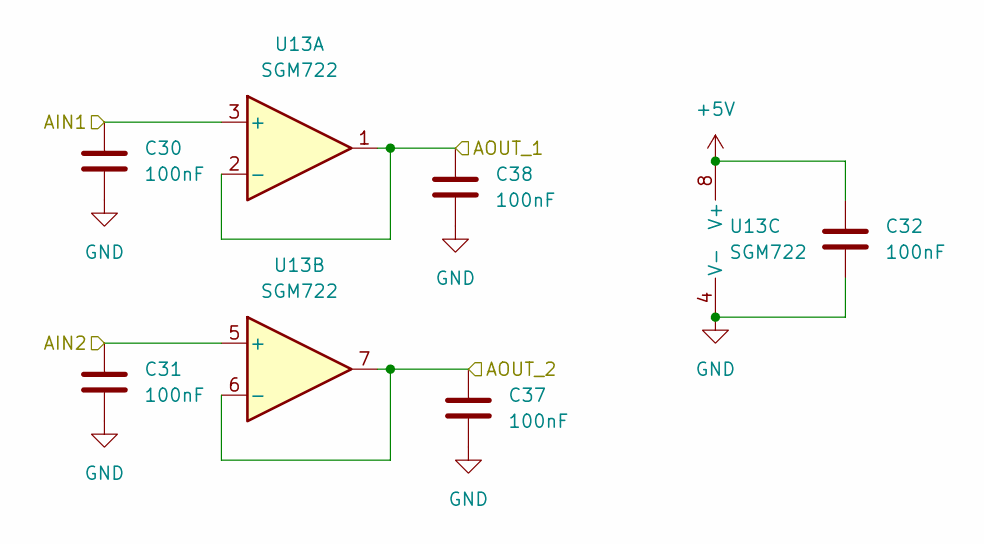
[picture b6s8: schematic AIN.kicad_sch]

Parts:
C30, C31, C32, C37, C38: 100nF; C_0805_2012Metric_Pad1.18x1.45mm_HandSolder_L
U13: SGM722; SOIC-8_3.9x4.9mm_P1.27mm_RMC_Handsolder

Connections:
+5V: C32.1, U13.8 (V+); also elsewhere on the board
BRAKE_AIN: C30.1, U13.3 (+); also elsewhere on the board
BRAKE_AIN_MCU: C38.2, U13.1, U13.2 (-); also elsewhere on the board
CURRENT_AIN: C31.1, U13.5 (+); also elsewhere on the board
CURRENT_MCU: C37.2, U13.6 (-), U13.7; also elsewhere on the board
GND: C30.2, C31.2, C32.2, C37.1, C38.1, U13.4 (V-); also elsewhere on the board

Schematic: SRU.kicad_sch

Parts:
CA1, CA2, CA3, CA4, CA5: 100nF; C_0805_2012Metric_Pad1.18x1.45mm_HandSolder_L
R33, R34, R35, R40, R41, R42, R43, R44: 1k; R_0805_2012Metric_Pad1.20x1.40mm_HandSolder_L
R36, R37, R38, R39: 10k; R_0805_2012Metric_Pad1.20x1.40mm_HandSolder_L
R45, R46, R47, R48: 4.7k; R_0805_2012Metric_Pad1.20x1.40mm_HandSolder_L
U10: 40106; SOIC127P600X175-14N
U11: LTV-847S; SMDIP-16_W9.53mm

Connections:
+5V: CA5.1, R45.2, R46.2, R47.2, R48.2, U10.14 (VDD); also elsewhere on the board
DIN5V_1: R45.1, U11.10; also elsewhere on the board
DIN5V_2: R46.1, U11.12; also elsewhere on the board
DIN5V_3: R47.1, U11.14; also elsewhere on the board
DIN_1: R33.1; also elsewhere on the board
DIN_2: R34.1; also elsewhere on the board
DIN_3: R35.1; also elsewhere on the board
GND: CA1.1, CA2.2, CA3.2, CA4.2, CA5.2, R36.2, R37.1, R38.2, R39.2, U10.7 (VSS), U11.2, U11.4, U11.6, U11.8, U11.9, U11.11, U11.13, U11.15; also elsewhere on the board
IGN_5V: R48.1, U11.16; also elsewhere on the board
IGN_12V: R40.1; also elsewhere on the board
unnamed: CA1.2, R33.2, R37.2, U10.1
unnamed: CA2.1, R34.2, R39.1, U10.3
unnamed: CA3.1, R35.2, R38.1, U10.5
unnamed: CA4.1, R36.1, R40.2, U10.9
unnamed: R41.1, U10.2
unnamed: R41.2, U11.7
unnamed: R42.1, U10.4
unnamed: R42.2, U11.5
unnamed: R43.1, U10.6
unnamed: R43.2, U11.3
unnamed: R44.1, U10.8
unnamed: R44.2, U11.1
